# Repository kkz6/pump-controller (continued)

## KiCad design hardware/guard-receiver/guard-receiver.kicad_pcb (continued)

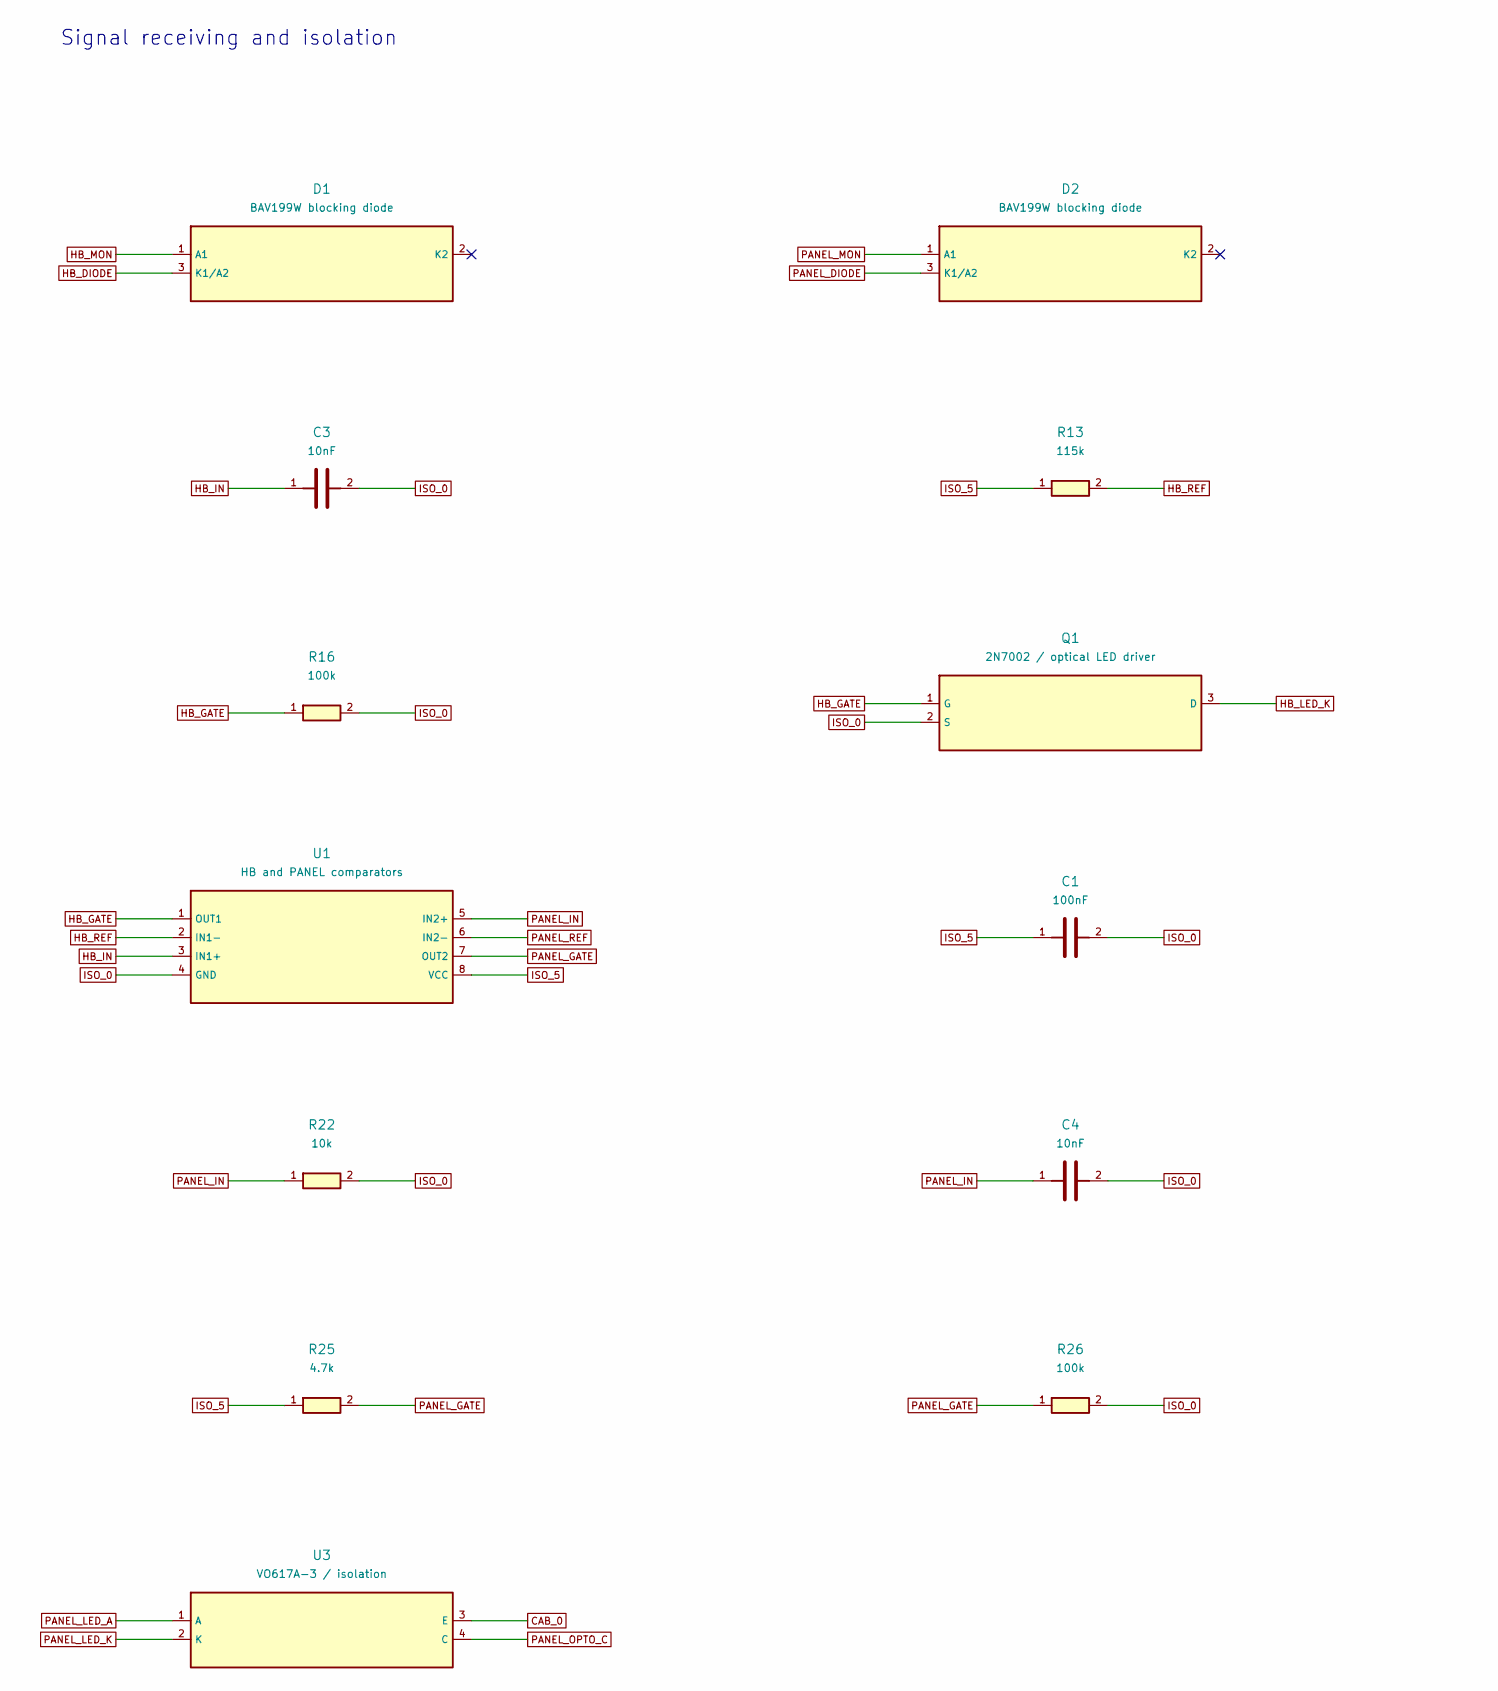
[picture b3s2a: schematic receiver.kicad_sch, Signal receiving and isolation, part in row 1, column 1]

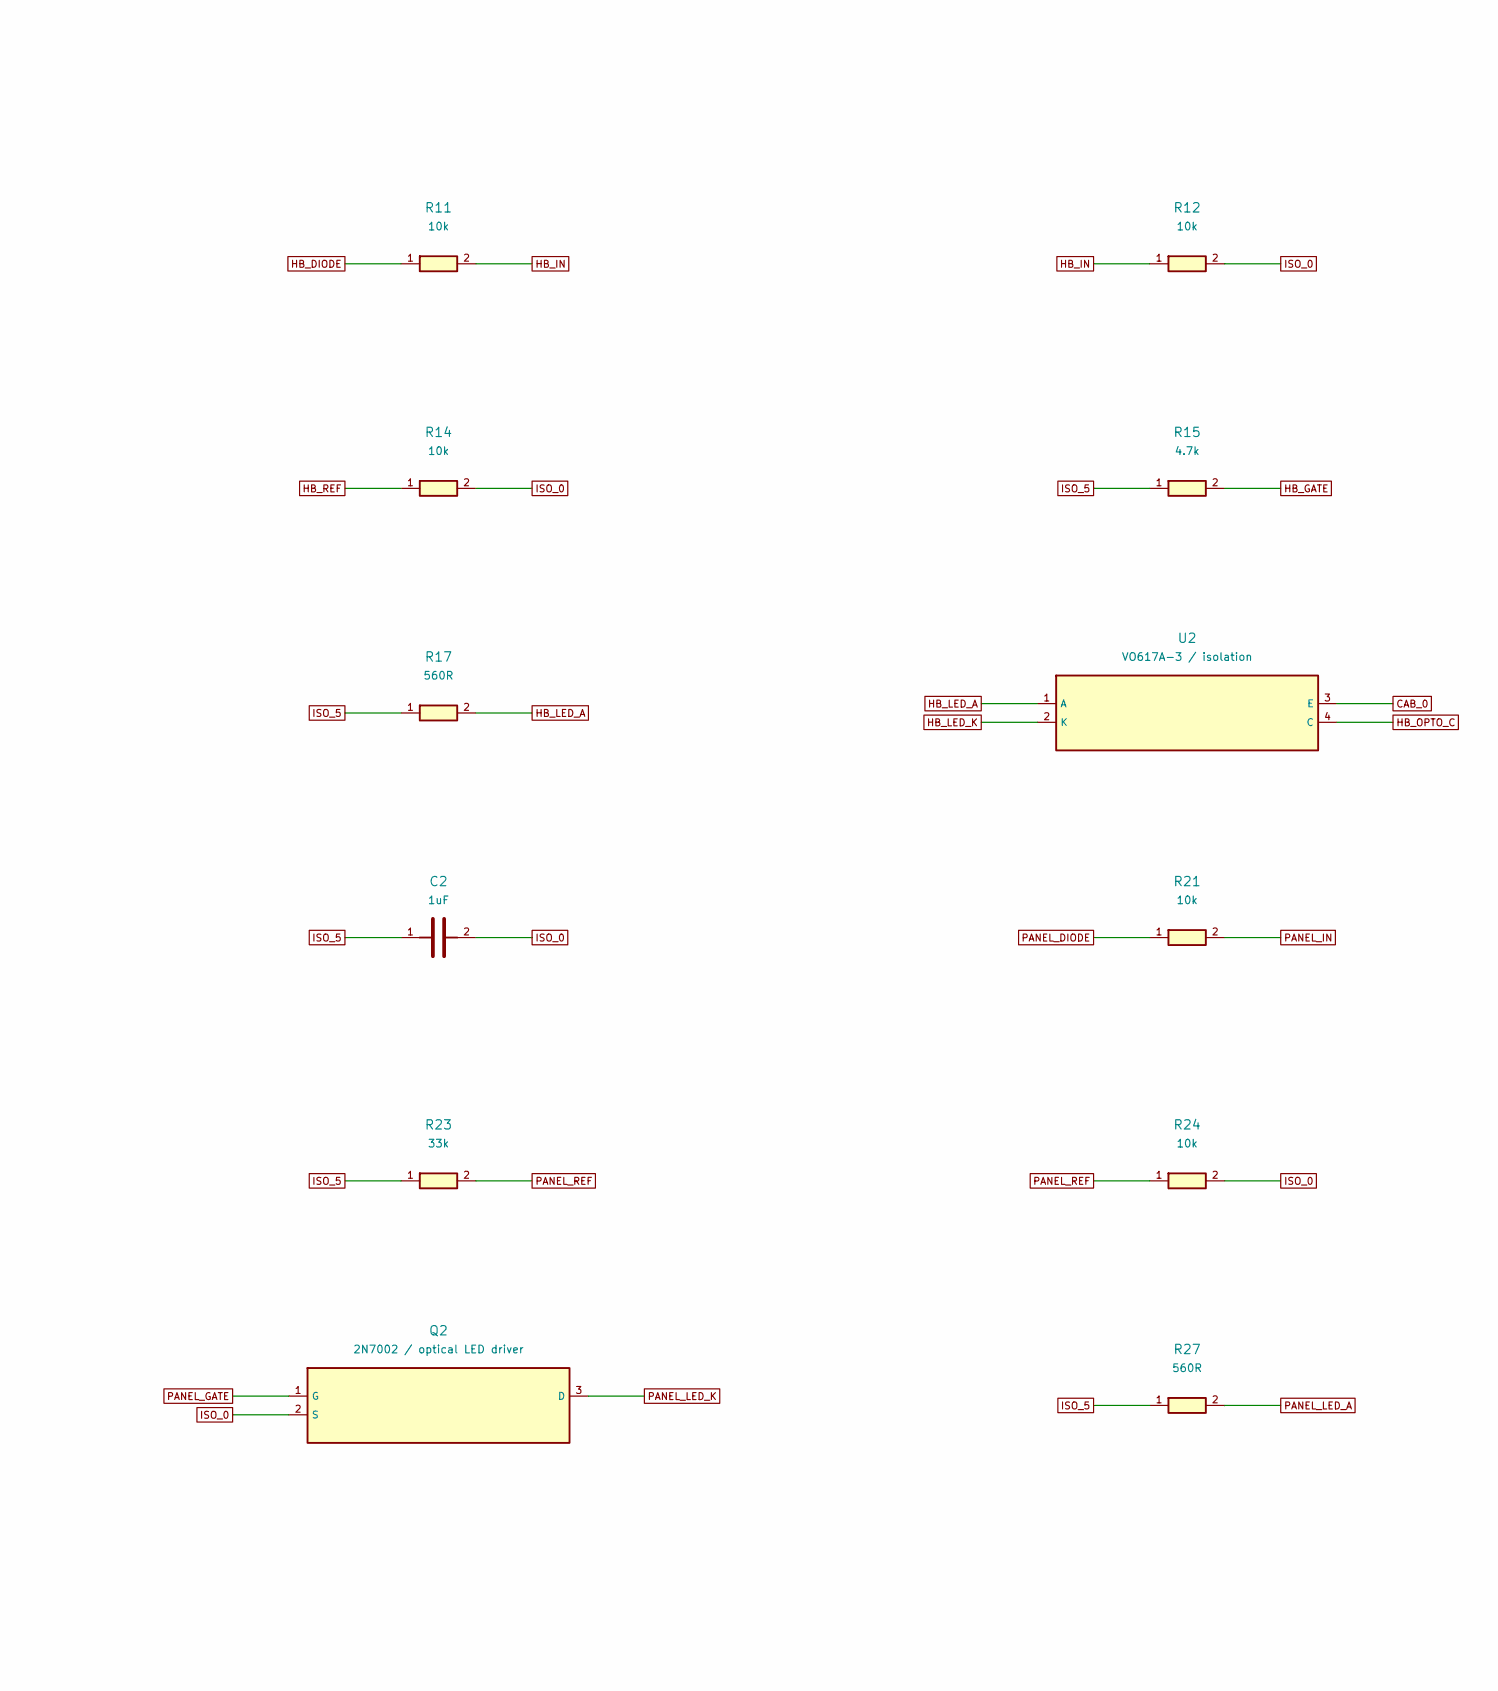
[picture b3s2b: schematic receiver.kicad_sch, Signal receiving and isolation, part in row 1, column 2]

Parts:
C1: 100nF; C_0805_2012Metric; MPN GRM21BR71H104KA01L
C2: 1uF; C_0805_2012Metric; MPN GRM21BR71C105KA01L
C3, C4: 10nF; C_0805_2012Metric; MPN GRM21BR71H103KA01L
D1, D2: BAV199W blocking diode; SOT-323_SC-70; MPN BAV199W,115
Q1, Q2: 2N7002 / optical LED driver; SOT-23; MPN 2N7002,215
R11, R12, R14, R21, R22, R24: 10k; R_0805_2012Metric; MPN RC0805FR-0710KL
R13: 115k; R_0805_2012Metric; MPN RC0805FR-07115KL
R15, R25: 4.7k; R_0805_2012Metric; MPN RC0805FR-074K7L
R16, R26: 100k; R_0805_2012Metric; MPN RC0805FR-07100KL
R17, R27: 560R; R_0805_2012Metric; MPN RC0805FR-07560RL
R23: 33k; R_0805_2012Metric; MPN RC0805FR-0733KL
U1: HB and PANEL comparators; SOIC-8_3.9x4.9mm_P1.27mm; MPN LM393BDR
U2, U3: VO617A-3 / isolation; DIP-4_W7.62mm; MPN VO617A-3

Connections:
CAB_0: U2.3 (E), U3.3 (E); also elsewhere on the board
HB_DIODE: D1.3 (K1/A2), R11.1
HB_GATE: Q1.1 (G), R15.2, R16.1, U1.1 (OUT1)
HB_IN: C3.1, R11.2, R12.1, U1.3 (IN1+)
HB_LED_A: R17.2, U2.1 (A)
HB_LED_K: Q1.3 (D), U2.2 (K)
HB_MON: D1.1 (A1); also elsewhere on the board
HB_OPTO_C: U2.4 (C); also elsewhere on the board
HB_REF: R13.2, R14.1, U1.2 (IN1-)
ISO_0: C1.2, C2.2, C3.2, C4.2, Q1.2 (S), Q2.2 (S), R12.2, R14.2, R16.2, R22.2, R24.2, R26.2, U1.4 (GND); also elsewhere on the board
ISO_5: C1.1, C2.1, R13.1, R15.1, R17.1, R23.1, R25.1, R27.1, U1.8 (VCC); also elsewhere on the board
PANEL_DIODE: D2.3 (K1/A2), R21.1
PANEL_GATE: Q2.1 (G), R25.2, R26.1, U1.7 (OUT2)
PANEL_IN: C4.1, R21.2, R22.1, U1.5 (IN2+)
PANEL_LED_A: R27.2, U3.1 (A)
PANEL_LED_K: Q2.3 (D), U3.2 (K)
PANEL_MON: D2.1 (A1); also elsewhere on the board
PANEL_OPTO_C: U3.4 (C); also elsewhere on the board
PANEL_REF: R23.2, R24.1, U1.6 (IN2-)

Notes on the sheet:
Signal receiving and isolation

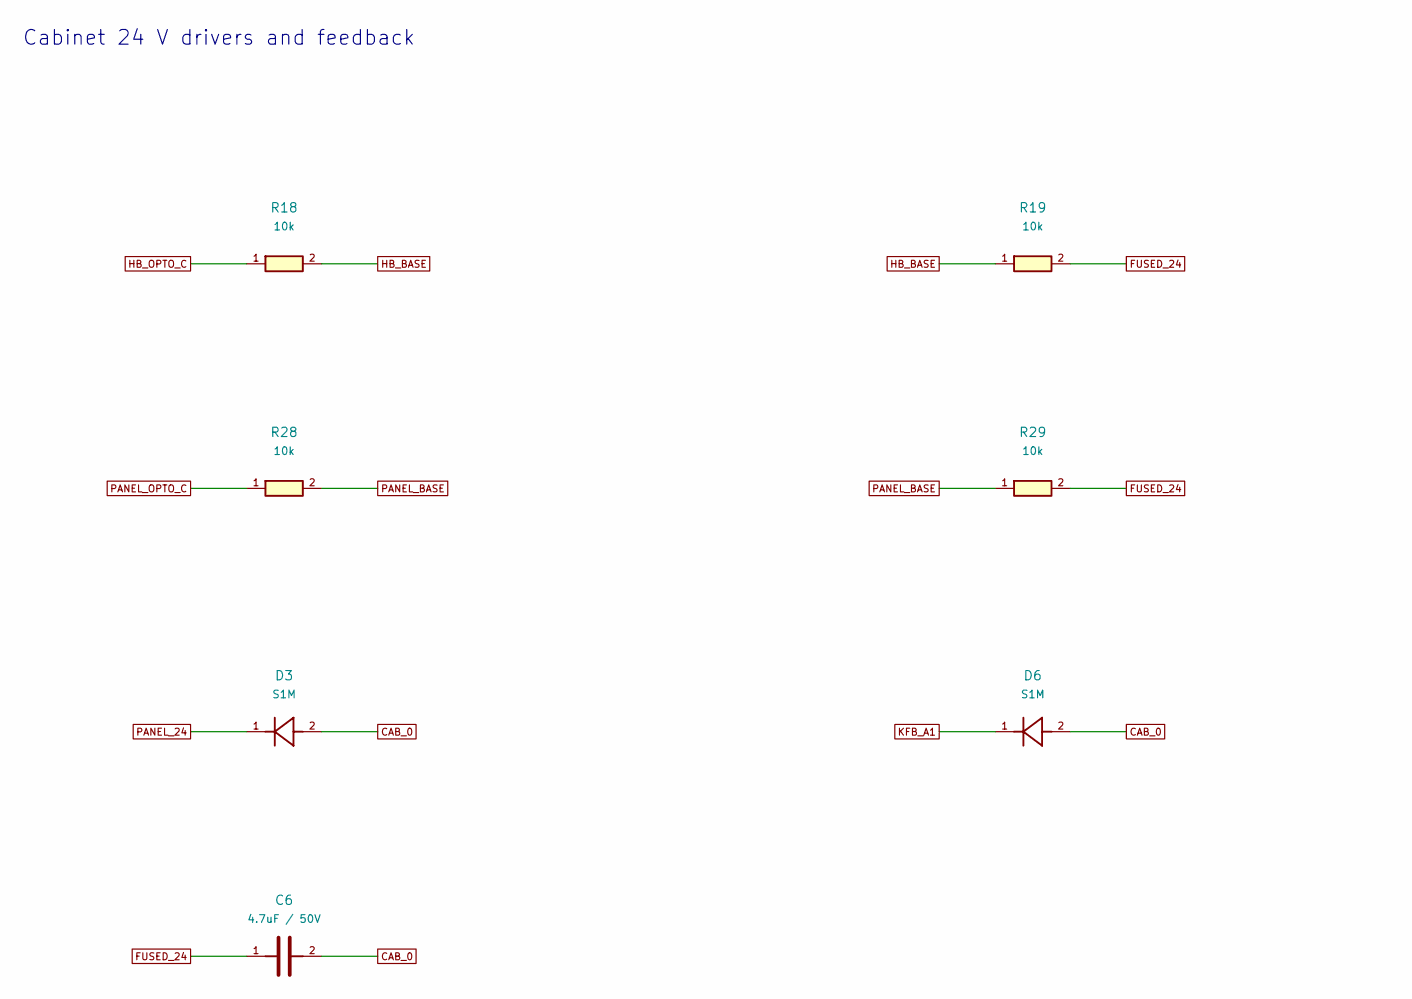
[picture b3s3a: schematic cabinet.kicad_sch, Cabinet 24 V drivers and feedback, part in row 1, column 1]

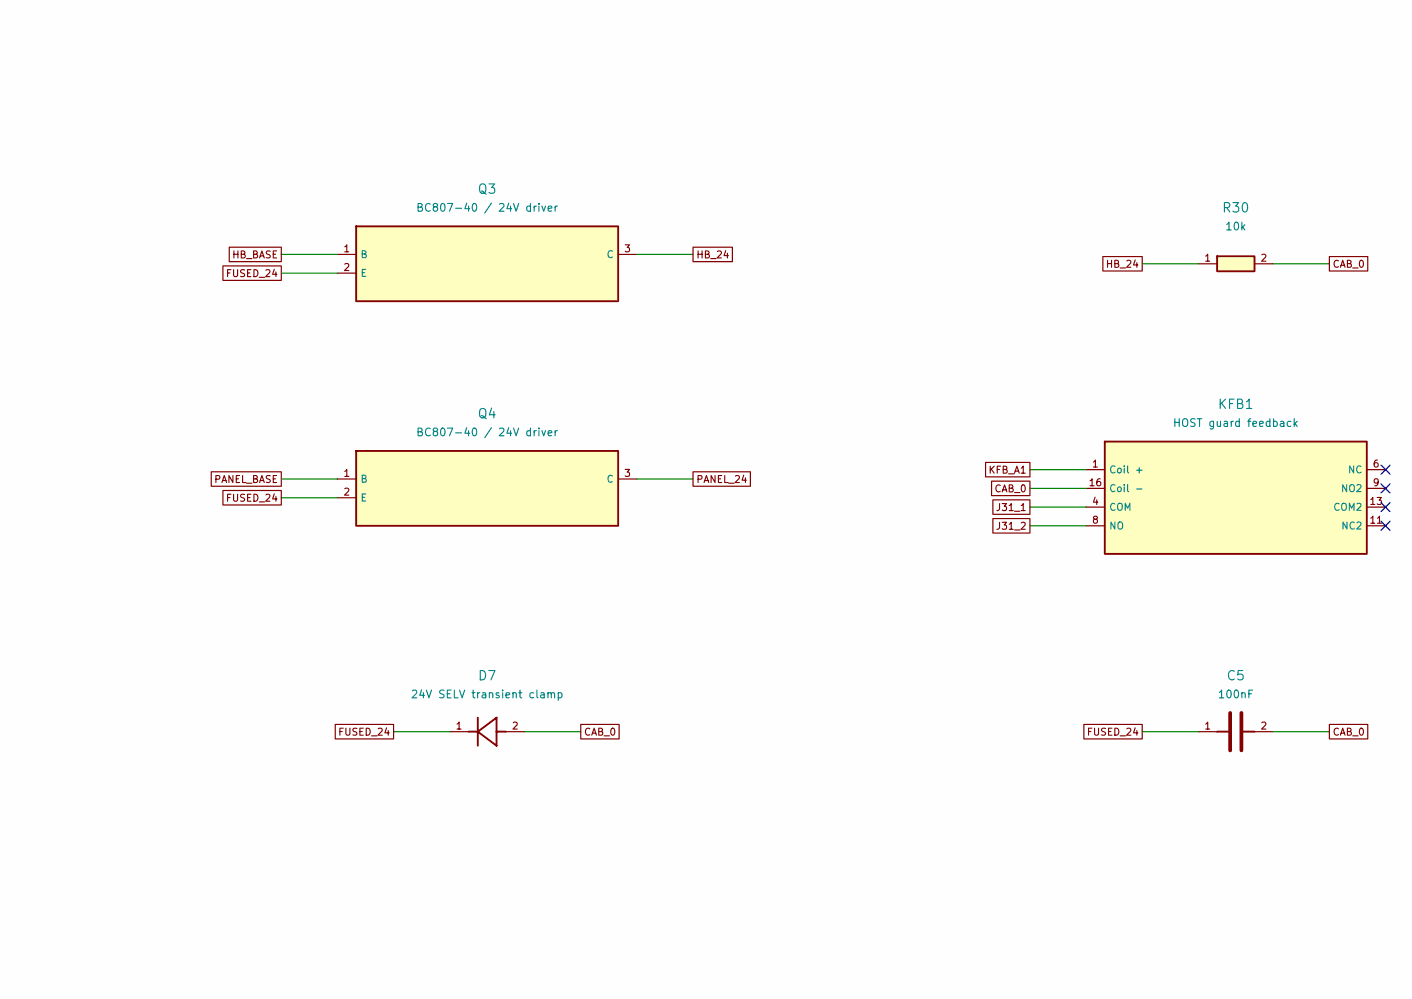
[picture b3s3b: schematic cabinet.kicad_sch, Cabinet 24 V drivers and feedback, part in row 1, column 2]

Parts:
C5: 100nF; C_0805_2012Metric; MPN GRM21BR71H104KA01L
C6: 4.7uF / 50V; C_1210_3225Metric; MPN GRM32ER71H475KA88L
D3, D6: S1M; D_SMA; MPN S1M-E3/61T
D7: 24V SELV transient clamp; D_SMB; MPN SMBJ26A-E3/52
KFB1: HOST guard feedback; Relay_DPDT_Omron_G5V-2; MPN G5V-2-H1 DC24
Q3, Q4: BC807-40 / 24V driver; SOT-23; MPN BC807-40,215
R18, R19, R28, R29, R30: 10k; R_0805_2012Metric; MPN RC0805FR-0710KL

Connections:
CAB_0: C5.2, C6.2, D3.2, D6.2, D7.2, KFB1.16 (Coil -), R30.2; also elsewhere on the board
FUSED_24: C5.1, C6.1, D7.1, Q3.2 (E), Q4.2 (E), R19.2, R29.2; also elsewhere on the board
HB_24: Q3.3 (C), R30.1; also elsewhere on the board
HB_BASE: Q3.1 (B), R18.2, R19.1
HB_OPTO_C: R18.1; also elsewhere on the board
J31_1: KFB1.4 (COM); also elsewhere on the board
J31_2: KFB1.8 (NO); also elsewhere on the board
KFB_A1: D6.1, KFB1.1 (Coil +); also elsewhere on the board
PANEL_24: D3.1, Q4.3 (C); also elsewhere on the board
PANEL_BASE: Q4.1 (B), R28.2, R29.1
PANEL_OPTO_C: R28.1; also elsewhere on the board

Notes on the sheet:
Cabinet 24 V drivers and feedback

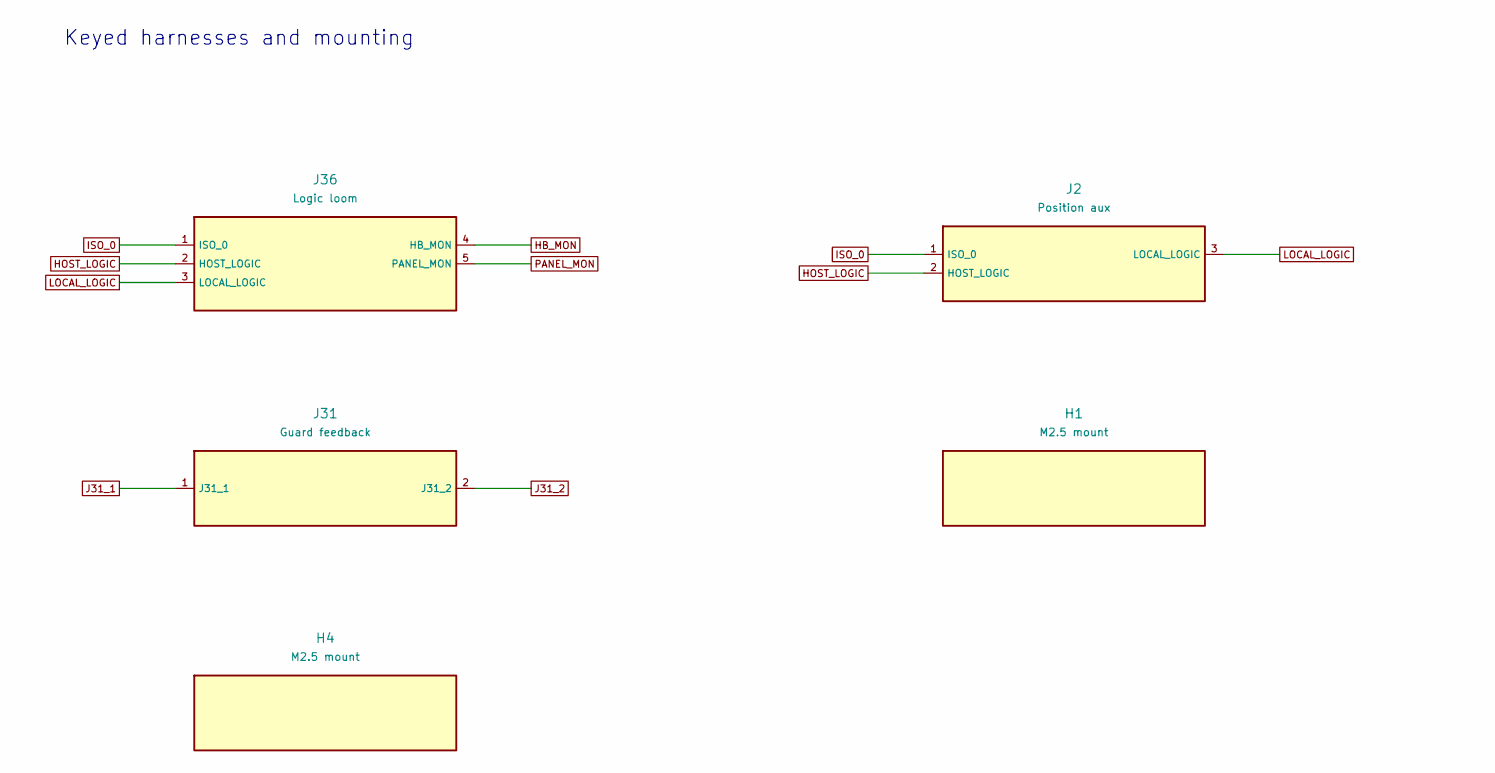
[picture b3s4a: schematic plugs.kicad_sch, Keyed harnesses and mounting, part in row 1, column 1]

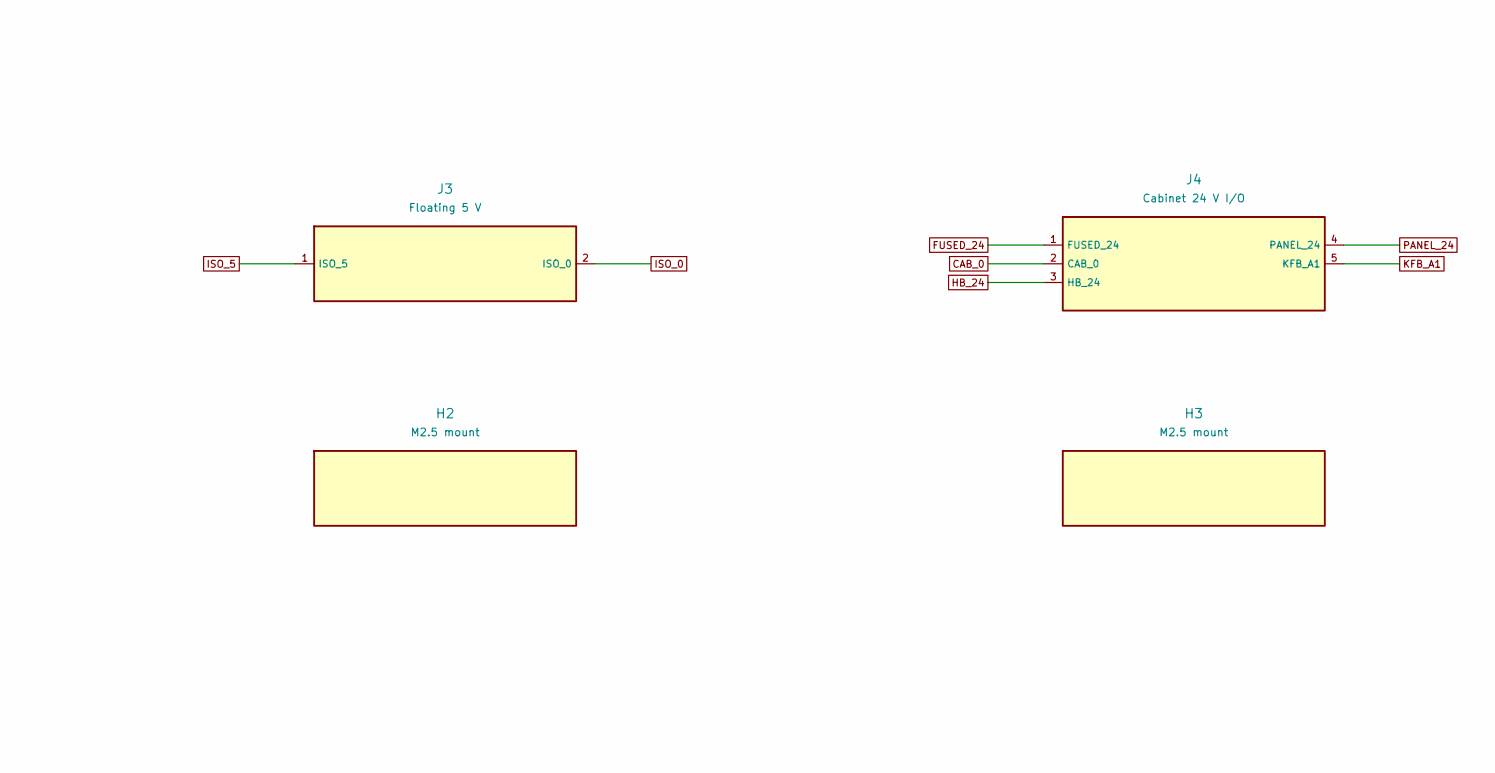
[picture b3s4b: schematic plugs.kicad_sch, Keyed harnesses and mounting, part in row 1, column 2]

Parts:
H1, H2, H3, H4: M2.5 mount; MountingHole_2.7mm_M2.5; MPN 2.7 mm NPTH
J2: Position aux; JST_PH_B3B-PH-K_1x03_P2.00mm_Vertical; MPN B3B-PH-K-S(LF)(SN)
J3: Floating 5 V; JST_PH_B2B-PH-K_1x02_P2.00mm_Vertical; MPN B2B-PH-K-S(LF)(SN)
J4: Cabinet 24 V I/O; JST_VH_S5P-VH_1x05_P3.96mm_Horizontal; MPN S5P-VH(LF)(SN)
J31: Guard feedback; PhoenixContact_MC_1,5_2-G-3.81_1x02_P3.81mm_Horizontal; MPN 1803277
J36: Logic loom; JST_ZE_S05B-ZESK-2D_1x05_P1.50mm_Horizontal; MPN S05B-ZESK-2D(T)(LF)(SN)

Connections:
CAB_0: J4.2 (CAB_0); also elsewhere on the board
FUSED_24: J4.1 (FUSED_24); also elsewhere on the board
HB_24: J4.3 (HB_24); also elsewhere on the board
HB_MON: J36.4 (HB_MON); also elsewhere on the board
HOST_LOGIC: J2.2 (HOST_LOGIC), J36.2 (HOST_LOGIC)
ISO_0: J2.1 (ISO_0), J3.2 (ISO_0), J36.1 (ISO_0); also elsewhere on the board
ISO_5: J3.1 (ISO_5); also elsewhere on the board
J31_1: J31.1 (J31_1); also elsewhere on the board
J31_2: J31.2 (J31_2); also elsewhere on the board
KFB_A1: J4.5 (KFB_A1); also elsewhere on the board
LOCAL_LOGIC: J2.3 (LOCAL_LOGIC), J36.3 (LOCAL_LOGIC)
PANEL_24: J4.4 (PANEL_24); also elsewhere on the board
PANEL_MON: J36.5 (PANEL_MON); also elsewhere on the board

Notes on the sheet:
Keyed harnesses and mounting

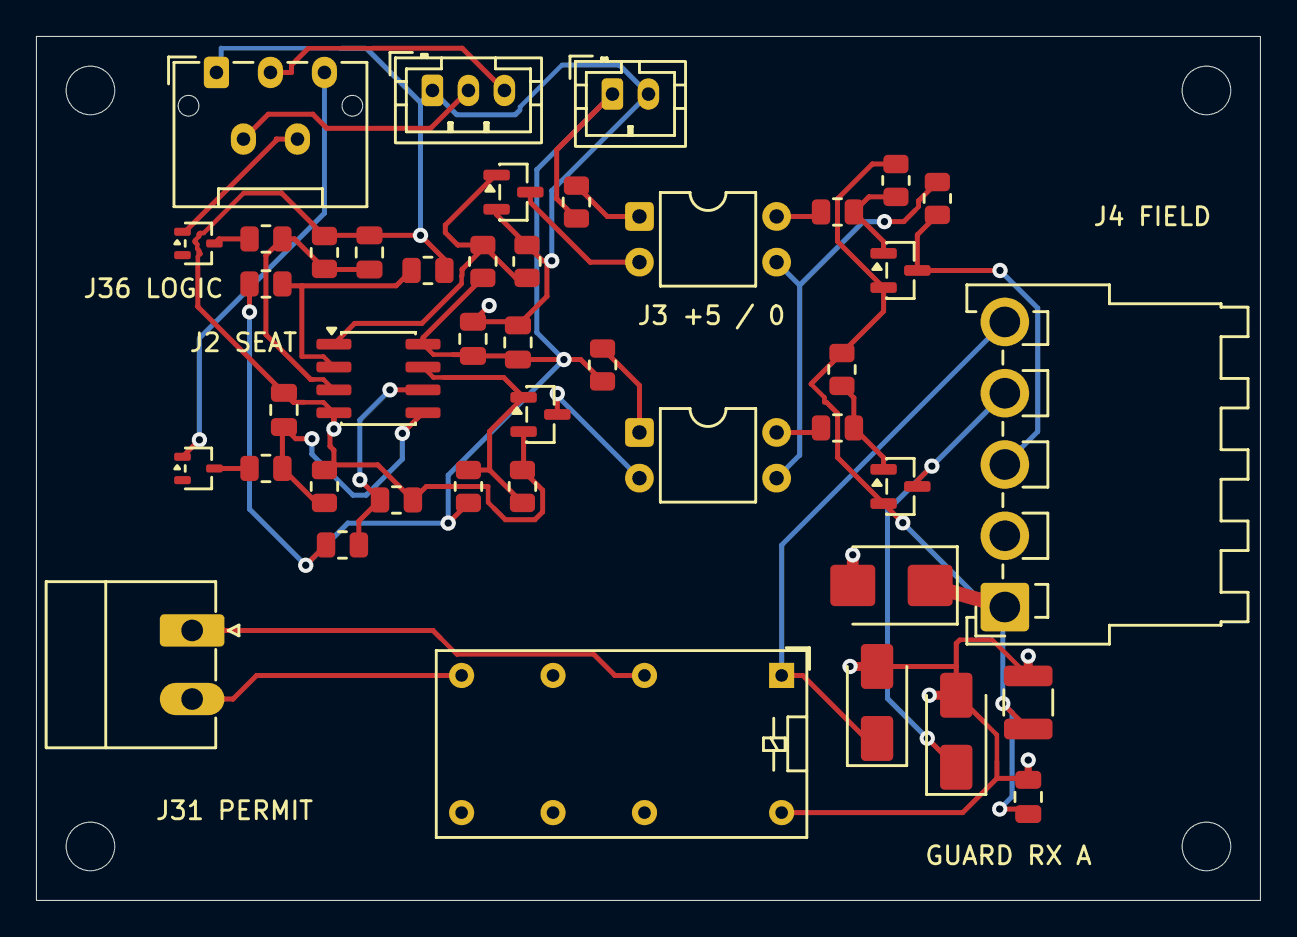
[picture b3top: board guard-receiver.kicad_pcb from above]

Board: 2 copper layers, 68.0 x 48.0 mm, 47 parts (0 on the bottom side), 29 nets.

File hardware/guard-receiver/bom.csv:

Reference,Value,MPN,Description,Footprint,Datasheet,Sheet,DNP
D1,BAV199W blocking diode,"BAV199W,115",Use diode 1 only. SC-70 pin 2 open.,Package_TO_SOT_SMD:SOT-323_SC-70,https://assets.nexperia.com/documents/data-sheet/BAV199W.pdf,receiver,False
D2,BAV199W blocking diode,"BAV199W,115",Use diode 1 only. SC-70 pin 2 open.,Package_TO_SOT_SMD:SOT-323_SC-70,https://assets.nexperia.com/documents/data-sheet/BAV199W.pdf,receiver,False
R11,10k,RC0805FR-0710KL,Yageo 1% 0805,Resistor_SMD:R_0805_2012Metric,,receiver,False
R12,10k,RC0805FR-0710KL,Yageo 1% 0805,Resistor_SMD:R_0805_2012Metric,,receiver,False
C3,10nF,GRM21BR71H103KA01L,"Murata X7R ceramic, nonpolar",Capacitor_SMD:C_0805_2012Metric,,receiver,False
R13,115k,RC0805FR-07115KL,Yageo 1% 0805,Resistor_SMD:R_0805_2012Metric,,receiver,False
R14,10k,RC0805FR-0710KL,Yageo 1% 0805,Resistor_SMD:R_0805_2012Metric,,receiver,False
R15,4.7k,RC0805FR-074K7L,Yageo 1% 0805,Resistor_SMD:R_0805_2012Metric,,receiver,False
R16,100k,RC0805FR-07100KL,Yageo 1% 0805,Resistor_SMD:R_0805_2012Metric,,receiver,False
Q1,2N7002 / optical LED driver,"2N7002,215",Nexperia SOT-23,Package_TO_SOT_SMD:SOT-23,https://assets.nexperia.com/documents/data-sheet/2N7002.pdf,receiver,False
R17,560R,RC0805FR-07560RL,Yageo 1% 0805,Resistor_SMD:R_0805_2012Metric,,receiver,False
U2,VO617A-3 / isolation,VO617A-3,Phototransistor DIP-4. Keep galvanic domains separate.,Package_DIP:DIP-4_W7.62mm,https://www.vishay.com/docs/83430/vo617a.pdf,receiver,False
U1,HB and PANEL comparators,LM393BDR,"TI dual comparator, SOIC-8.",Package_SO:SOIC-8_3.9x4.9mm_P1.27mm,https://www.ti.com/lit/ds/symlink/lm393b.pdf,receiver,False
C1,100nF,GRM21BR71H104KA01L,"Murata X7R ceramic, nonpolar",Capacitor_SMD:C_0805_2012Metric,,receiver,False
C2,1uF,GRM21BR71C105KA01L,"Murata X7R ceramic, nonpolar",Capacitor_SMD:C_0805_2012Metric,,receiver,False
R21,10k,RC0805FR-0710KL,Yageo 1% 0805,Resistor_SMD:R_0805_2012Metric,,receiver,False
R22,10k,RC0805FR-0710KL,Yageo 1% 0805,Resistor_SMD:R_0805_2012Metric,,receiver,False
C4,10nF,GRM21BR71H103KA01L,"Murata X7R ceramic, nonpolar",Capacitor_SMD:C_0805_2012Metric,,receiver,False
R23,33k,RC0805FR-0733KL,Yageo 1% 0805,Resistor_SMD:R_0805_2012Metric,,receiver,False
R24,10k,RC0805FR-0710KL,Yageo 1% 0805,Resistor_SMD:R_0805_2012Metric,,receiver,False
R25,4.7k,RC0805FR-074K7L,Yageo 1% 0805,Resistor_SMD:R_0805_2012Metric,,receiver,False
R26,100k,RC0805FR-07100KL,Yageo 1% 0805,Resistor_SMD:R_0805_2012Metric,,receiver,False
Q2,2N7002 / optical LED driver,"2N7002,215",Nexperia SOT-23,Package_TO_SOT_SMD:SOT-23,https://assets.nexperia.com/documents/data-sheet/2N7002.pdf,receiver,False
R27,560R,RC0805FR-07560RL,Yageo 1% 0805,Resistor_SMD:R_0805_2012Metric,,receiver,False
U3,VO617A-3 / isolation,VO617A-3,Phototransistor DIP-4. Keep galvanic domains separate.,Package_DIP:DIP-4_W7.62mm,https://www.vishay.com/docs/83430/vo617a.pdf,receiver,False
R18,10k,RC0805FR-0710KL,Yageo 1% 0805,Resistor_SMD:R_0805_2012Metric,,cabinet,False
R19,10k,RC0805FR-0710KL,Yageo 1% 0805,Resistor_SMD:R_0805_2012Metric,,cabinet,False
Q3,BC807-40 / 24V driver,"BC807-40,215",Nexperia SOT-23,Package_TO_SOT_SMD:SOT-23,https://assets.nexperia.com/documents/data-sheet/BC807_SER.pdf,cabinet,False
R30,10k,RC0805FR-0710KL,Yageo 1% 0805,Resistor_SMD:R_0805_2012Metric,,cabinet,False
R28,10k,RC0805FR-0710KL,Yageo 1% 0805,Resistor_SMD:R_0805_2012Metric,,cabinet,False
R29,10k,RC0805FR-0710KL,Yageo 1% 0805,Resistor_SMD:R_0805_2012Metric,,cabinet,False
Q4,BC807-40 / 24V driver,"BC807-40,215",Nexperia SOT-23,Package_TO_SOT_SMD:SOT-23,https://assets.nexperia.com/documents/data-sheet/BC807_SER.pdf,cabinet,False
KFB1,HOST guard feedback,G5V-2-H1 DC24,"Omron single-side stable, isolated bifurcated gold-alloy NO.",Relay_THT:Relay_DPDT_Omron_G5V-2,https://omronfs.omron.com/en_US/ecb/products/pdf/en-g5v_2.pdf,cabinet,False
D3,S1M,S1M-E3/61T,SMA suppression diode. Band to coil positive.,Diode_SMD:D_SMA,https://www.vishay.com/docs/88711/s1a.pdf,cabinet,False
D6,S1M,S1M-E3/61T,SMA suppression diode. Band to coil positive.,Diode_SMD:D_SMA,https://www.vishay.com/docs/88711/s1a.pdf,cabinet,False
D7,24V SELV transient clamp,SMBJ26A-E3/52,"Unidirectional 26 V TVS, use a regulated 24 V rail.",Diode_SMD:D_SMB,https://www.vishay.com/docs/88392/smbj.pdf,cabinet,False
C5,100nF,GRM21BR71H104KA01L,"Murata X7R ceramic, nonpolar",Capacitor_SMD:C_0805_2012Metric,,cabinet,False
C6,4.7uF / 50V,GRM32ER71H475KA88L,Murata X7R ceramic 1210; nonpolar.,Capacitor_SMD:C_1210_3225Metric,,cabinet,False
J36,Logic loom,S05B-ZESK-2D(T)(LF)(SN),,Connector_JST:JST_ZE_S05B-ZESK-2D_1x05_P1.50mm_Horizontal,,plugs,False
J2,Position aux,B3B-PH-K-S(LF)(SN),,Connector_JST:JST_PH_B3B-PH-K_1x03_P2.00mm_Vertical,,plugs,False
J3,Floating 5 V,B2B-PH-K-S(LF)(SN),,Connector_JST:JST_PH_B2B-PH-K_1x02_P2.00mm_Vertical,,plugs,False
J4,Cabinet 24 V I/O,S5P-VH(LF)(SN),,Connector_JST:JST_VH_S5P-VH_1x05_P3.96mm_Horizontal,,plugs,False
J31,Guard feedback,1803277,,"Connector_Phoenix_MC:PhoenixContact_MC_1,5_2-G-3.81_1x02_P3.81mm_Horizontal",,plugs,False
H1,M2.5 mount,2.7 mm NPTH,,MountingHole:MountingHole_2.7mm_M2.5,,plugs,False
H2,M2.5 mount,2.7 mm NPTH,,MountingHole:MountingHole_2.7mm_M2.5,,plugs,False
H3,M2.5 mount,2.7 mm NPTH,,MountingHole:MountingHole_2.7mm_M2.5,,plugs,False
H4,M2.5 mount,2.7 mm NPTH,,MountingHole:MountingHole_2.7mm_M2.5,,plugs,False

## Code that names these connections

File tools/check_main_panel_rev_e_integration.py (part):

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host_map=[]
service_interlock = main_source.get('revision') in ('COMPACT-DUAL-GUARD-R3','INTEGRATED-R4')
for pin,(ref,num)in enumerate([('J32',i)for i in range(1,13)],1):
 mn=mainnet(ref,num);pn=net('J1',pin);expect= {'KEY_MAN_N':'SPARE_B6','KEY_AUTO_N':'SPARE_B7'}.get(pn,pn)
 if pin==1 and service_interlock:expect='+5V_CMD'
 if mn!=expect:issues.append('host harness mismatch pin '+str(pin))
 host_map.append({'panel_pin':pin,'panel_net':pn,'main_connector':ref,'main_pin':num,'main_net':mn})
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                            'return_live_without_bridge': before_bridge, 'return_live_with_bridge': after_bridge})
if [net('J7',i)for i in range(1,5)]!=['I2C_SCL','I2C_SDA','GND','+3V3']:issues.append('OLED connector order mismatch')
keychecks=[]
for q,jpin,raw,bn,out,refs in [('Q1',2,'KEY_MAN_RAW','KEY_MAN_B','KEY_MAN_N',['R2','R3','R4','R5','C3']),('Q2',3,'KEY_AUTO_RAW','KEY_AUTO_B','KEY_AUTO_N',['R6','R7','R8','R9','C4'])]:
 if [net(q,i)for i in (1,2,3)]!=[bn,'GND',out]:issues.append('NPN pinout mismatch '+q)
 if net('J8',1)!='+5V'or net('J8',jpin)!=raw:issues.append('key raw pin map mismatch')
 for ref,val,pair in zip(refs,['2.2k','10k','100k','10k','10nF'],[(raw,'GND'),(raw,bn),(bn,'GND'),('+3V3',out),(out,'GND')]):
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   if key not in str(board_fps[ref].GetFPID().GetLibItemName()):
    issues.append('Mechanically keyed connector footprint mismatch: ' + ref)
  if any(ref.startswith('SW') for ref in mainfps):issues.append('Physical switch footprint on button-free main PCB')
  for pin, name in [('8', 'START_CMD_LED'), ('28', 'STOP_CMD_LED')]:
   if mainnet('U33', pin) != name or sp[pin].get('type') != 'output':
    issues.append('Incorrect compact-dual command LED direction or signal at U33.' + pin)
  for ref in ('SW1','SW2','SW3','SW4','SW5'):
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
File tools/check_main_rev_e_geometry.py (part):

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            source_issues.append({'ref': ref, 'issue': 'original electrical component missing'})
            continue
        old_pins = {str(x['num']): x.get('net') or '' for x in old['pins']}
        conditioner_raw_pins = {'R80': ('2','STOP_SENSE_RAW'), 'R81': ('1','STOP_SENSE_RAW'), 'C80': ('1','STOP_SENSE_RAW'),
                                'R82': ('2','MAN_SENSE_RAW'), 'R83': ('1','MAN_SENSE_RAW'), 'C82': ('1','MAN_SENSE_RAW'),
                                'R84': ('2','AUTO_SENSE_RAW'), 'R85': ('1','AUTO_SENSE_RAW'), 'C84': ('1','AUTO_SENSE_RAW')}
        if ref in conditioner_raw_pins:
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        if ref in conditioner_values and new['value'] != conditioner_values[ref]:
            source_issues.append({'ref': ref, 'issue': 'conditioner divider/filter value mismatch', 'expected': conditioner_values[ref], 'actual': new['value']})
        if ref == 'U31':
            old_pins['6'] = 'ARM_CLEAR_N'
        if compact and ref == 'U33':
            old_pins.update({'8': '', '21': 'SPARE_B7'})
            if has_indicators:
                old_pins.update({'8': 'START_CMD_LED', '28': 'STOP_CMD_LED'})
            if dual:
                old_pins.update({'24': 'HOST_SENSE_N', '23': 'LOCAL_SENSE_N'})
            pin_types = {str(pin['num']): pin['type'] for pin in new['pins']}
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                                'I2C_SCL', 'SPARE_B6', 'SPARE_B7']))
            old_pins['MP'] = 'GND'
        if dual and ref == 'K1':
            old_pins.update({'2': 'CTRL_A_COM', '3': 'CTRL_A_NO'})
        if dual and ref == 'K2':
            old_pins.update({'2': 'CTRL_B_COM', '3': 'CTRL_B_NO'})
        if dual and ref == 'J30':
            old_pins = {'1': 'CTRL_A_COM', '2': 'CTRL_A_NO'}
        if usb_service and ref in ('K2', 'D32', 'J32'):
            old_pins['1'] = '+5V_CMD'
        if usb_service and ref == 'U1':
            old_pins['5'] = 'PSU_5V_RAW'
        if usb_service and ref == 'J2':
            del old_pins['7'], old_pins['8']
        new_pins = {str(x['num']): x.get('net') or '' for x in new['pins']}
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
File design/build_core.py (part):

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# All M_* nets, including M_GND, are LIVE. Only U11 crosses the isolation barrier.
s=sheet('meter_ic','Single-phase metering - LIVE DOMAIN','M_GND is bonded to neutral; it is NEVER sensor ground. 230 V nominal, 264 V maximum design input.')
url='https://www.analog.com/media/en/technical-documentation/data-sheets/ade7953.pdf'
pinmap=[(1,'ZX',None,'output'),(2,'RESET_N','M_RESET_N','input'),(3,'VINTD','M_VINTD','power_out'),(4,'DGND','M_GND','power_in'),
(5,'IAP','M_IAP','input'),(6,'IAN','M_IAN','input'),(7,'PULL_HIGH','M_3V3','input'),(8,'PULL_HIGH','M_3V3','input'),
(9,'IBP','M_GND','input'),(10,'IBN','M_GND','input'),(11,'VN','M_VN','input'),(12,'VP','M_VP','input'),(13,'REF','M_REF','power_out'),
(14,'PULL_LOW','M_GND','input'),(15,'VINTA','M_VINTA','power_out'),(16,'AGND','M_GND','power_in'),(17,'VDD','M_3V3','power_in'),
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conn(s,'J31',['STOP_RETURN','K1_COIL_PLUS'],'STOP-fed high-high NC float loop / fitted shorting link')

s=sheet('local_controls','External MODE and onboard settings controls','Rev C: existing START/STOP actuators plus one external MODE button. SW3 SET and SW4 NEXT are on the PCB. STOP/HH clear ARM; mode/settings require STOP event, release and unarmed state.')
j32=conn(s,'J32',['+5V','STOP_RETURN','MAN_RETURN','AUTO_RETURN','START_N','RESET_N','GND'],'External STOP / START / MODE; pins4,6 reserved')
for pin,name in zip(j32['pins'],['STOP_NC_SUPPLY','STOP_NC_RETURN','MODE_NO_RETURN','RESERVED_NEXT','START_NO','RESERVED_SET','BUTTON_GND']):pin['name']=name
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# MCP23017 port A is spare, B reads contacts. 0x20 at 400 kHz.
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        if comp['ref'] in source_urls:
            comp['datasheet'] = source_urls[comp['ref']]
        for pin in comp['pins']:
            if pin.get('net')=='M_ISO_RETURN':pin['net']='M_ISO_GND'
BASE.joinpath('core.json').write_text(json.dumps({'sheets':S},indent=2))
print('Core',sum(len(s['components']) for s in S),'components including external CT/burden/OLED')

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
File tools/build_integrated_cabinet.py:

"""Build the R4 field schematic, BOM and native ERC/PDF/netlist for the two-PCB system."""
import argparse
import json
import os
from pathlib import Path
import shutil
import subprocess
import xml.etree.ElementTree as ET

import build_starter_guard as field
import generate_cad as cad

PROJECT = "starter-guard-r4"
OUT = cad.BASE / "hardware" / PROJECT


def design():
    instruments, outputs, service = field.field(OUT / "contacts.csv")
    # The internal feedback switch and its suppressor now live entirely on the main PCB.
    instruments = [part for part in instruments if part["ref"] != "D3"]
    outputs = [part for part in outputs if part["ref"] not in {"J31", "KFB1", "D6"}]
    for part in instruments:
        if part["ref"] == "XF3":
            for pin in part["pins"]:
                pin["net"] = {"HOST_LOGIC": "HOST_AUX_N", "LOCAL_LOGIC": "LOCAL_AUX_N",
                              "ISO_0": "GND"}.get(pin["net"], pin["net"])
    instruments.extend([
        field.part("J52", "Main selector auxiliary mating plug", "JST PHR-3 / SPH-002T-P0.5S",
                   [(1, "Logic common", "GND"), (2, "HOST dry pole", "HOST_AUX_N"),
                    (3, "LOCAL dry pole", "LOCAL_AUX_N")],
                   "Low-level isolated transfer auxiliary. Only these three cores share the main logic domain."),
        field.part("J54", "Main cabinet I/O mating plug", "JST VHR-5N / SVH-21T-P1.1",
                   [(1, "Fused +24 V", "FUSED_24"), (2, "Cabinet 0 V", "CAB_0"),
                    (3, "PNP heartbeat", "HB_24"), (4, "Panel relay +", "PANEL_24"),
                    (5, "Host feedback +", "KFB_A1")],
                   "Field-side 24 V only. At the main PCB, pin 5 feeds the onboard feedback relay coil."),
    ])
    # Illustrate the factory pilot explicitly, using functional OEM terminal names.
    # The common trip chain uses spare electrically isolated contact poles.
    factory_poles = {
        "S3": [("OEM-IN", "Original STOP NC", "OEM_CTRL_L"), ("OEM-OUT", "Original STOP NC", "PILOT_AFTER_STOP")],
        "S4": [("OEM-IN", "Original overload NC", "PILOT_AFTER_STOP"), ("OEM-OUT", "Original overload NC", "PILOT_P")],
        "S5": [("OEM-IN", "Original START NO", "PILOT_P"), ("OEM-OUT", "Original START NO", "PILOT_D")],
        "KOF1": [("A1", "OEM coil +", "PILOT_D"), ("A2", "OEM coil return", "PILOT_COIL_RETURN")],
    }
    for part in instruments:
        for number, name, net in factory_poles.get(part["ref"], []):
            part["pins"].append(dict(num=number, name=name, net=net, type="passive"))
    pilot = field.pilot_profile()
    pilot.append(field.part(
        "XPF1", "DOL service plug mating positions", "Same XC1 profile-matched break-before-make transfer",
        [("H1", "XC1.1 HOST", "B_COM"), ("F1", "Field P", "PILOT_P"),
         ("H2", "XC1.2 HOST", "B_NO"), ("F2", "Field D", "PILOT_D"),
         ("H3", "XC1.3 HOST", "A_COM"), ("F3", "Coil return", "PILOT_COIL_RETURN"),
         ("H4", "XC1.4 HOST", "A_NO"), ("F4", "Pilot 0 V", "OEM_CTRL_N"),
         ("L3", "LOCAL link in", "PILOT_COIL_RETURN"), ("L4", "LOCAL link out", "OEM_CTRL_N")],
        "Functional view of the XC1 inserts, not an additional device. HOST connects H1-F1 through H4-F4. LOCAL connects only L3-L4. All are open during transfer."))
    for part in outputs + pilot:
        if part["ref"] == "XM2":
            part["description"] = "Motor L and N only. Segregate from J52, J54 and XC1. Keep PE continuous on the separate earth bar. Fit rail end stops and 3047028 end covers."
        elif part["ref"] == "XP10":
            part["description"] = "KS1/KS2 interrupt the motor feeder. The SELV pilot stays powered. Only for the verified 24 V DC pilot profile."
    sheets = [
        ("field", "Independent trips and main board interfaces", instruments),
        ("outputs", "Guard relays and series motor contactors", outputs),
        ("pilot", "Conventional 24 V DC pilot proof", pilot),
        ("service", "Motor isolator and USB access interlock", service),
    ]
    return {"project": PROJECT, "revision": "R4", "title": "Independent external starter guard",
            "sheets": [dict(id=s, title=t, components=c) for s,t,c in sheets]}


def main():
    parser = argparse.ArgumentParser(description=__doc__)
    parser.add_argument("--check", action="store_true", help="Run KiCad ERC and export the field drawing and netlist")
    args = parser.parse_args()
    data = design()
    cad.write_schematics(data, OUT, PROJECT)
    cad.write_bom(data, OUT)
    (OUT / (PROJECT + ".kicad_pro")).write_text(json.dumps(
        {"meta": {"filename": PROJECT + ".kicad_pro", "version": 3}}, indent=2) + "\n")
    if not args.check:
        return
    cli = os.environ.get("KICAD_CLI") or shutil.which("kicad-cli") or str(cad.BASE / ".tools/kicad-cli")
    checks = OUT / "checks"
    checks.mkdir(exist_ok=True)
    jobs = [
        ("erc", "--format", "json", "--severity-all", "--exit-code-violations", "-o", "checks/erc.json"),
        ("export", "netlist", "--format", "kicadxml", "-o", "checks/guard-netlist.xml"),
        ("export", "pdf", "-o", "guard-schematic.pdf"),
    ]
    for job in jobs:
        subprocess.run([cli, "sch", *job, PROJECT + ".kicad_sch"], cwd=OUT, check=True)
    netlist = checks / "guard-netlist.xml"
    cad.validate_netlist(data, netlist)
    xml = ET.parse(netlist)
    for element in xml.findall(".//source") + xml.findall(".//uri"):
        if element.text:
            element.text = element.text.replace(str(OUT) + "/", "")
    xml.write(netlist, encoding="utf-8", xml_declaration=True)
    ercfile = checks / "erc.json"
    erc = json.loads(ercfile.read_text())
    for sheet in erc["sheets"]:
        if "source" in sheet:
            sheet["source"] = Path(sheet["source"]).name
    ercfile.write_text(json.dumps(erc, indent=2) + "\n")


if __name__ == "__main__":
    main()
